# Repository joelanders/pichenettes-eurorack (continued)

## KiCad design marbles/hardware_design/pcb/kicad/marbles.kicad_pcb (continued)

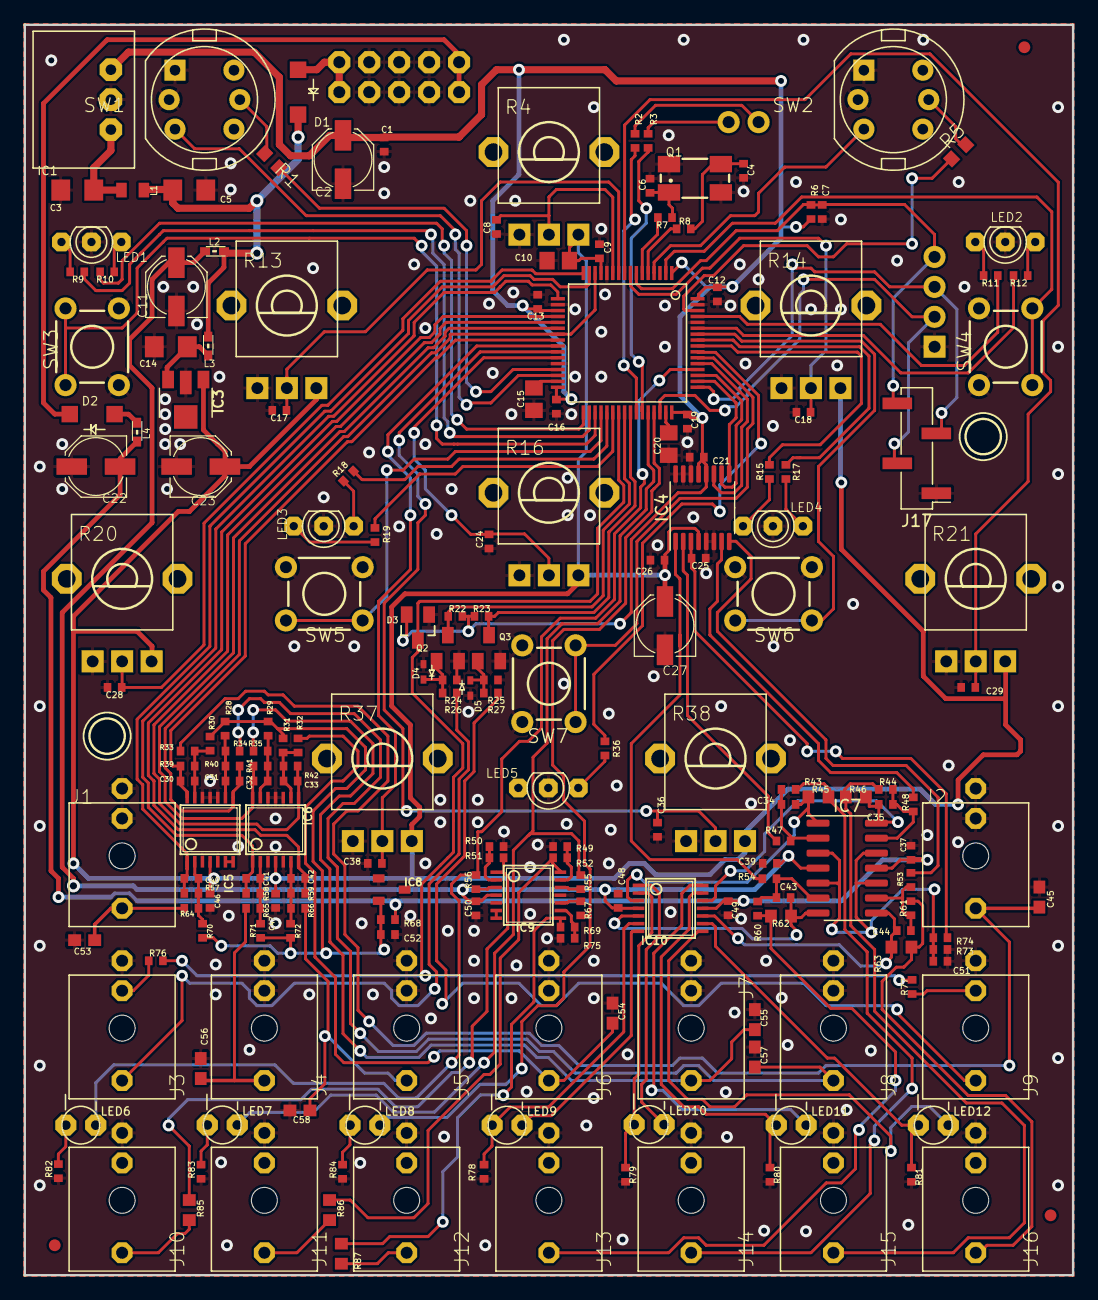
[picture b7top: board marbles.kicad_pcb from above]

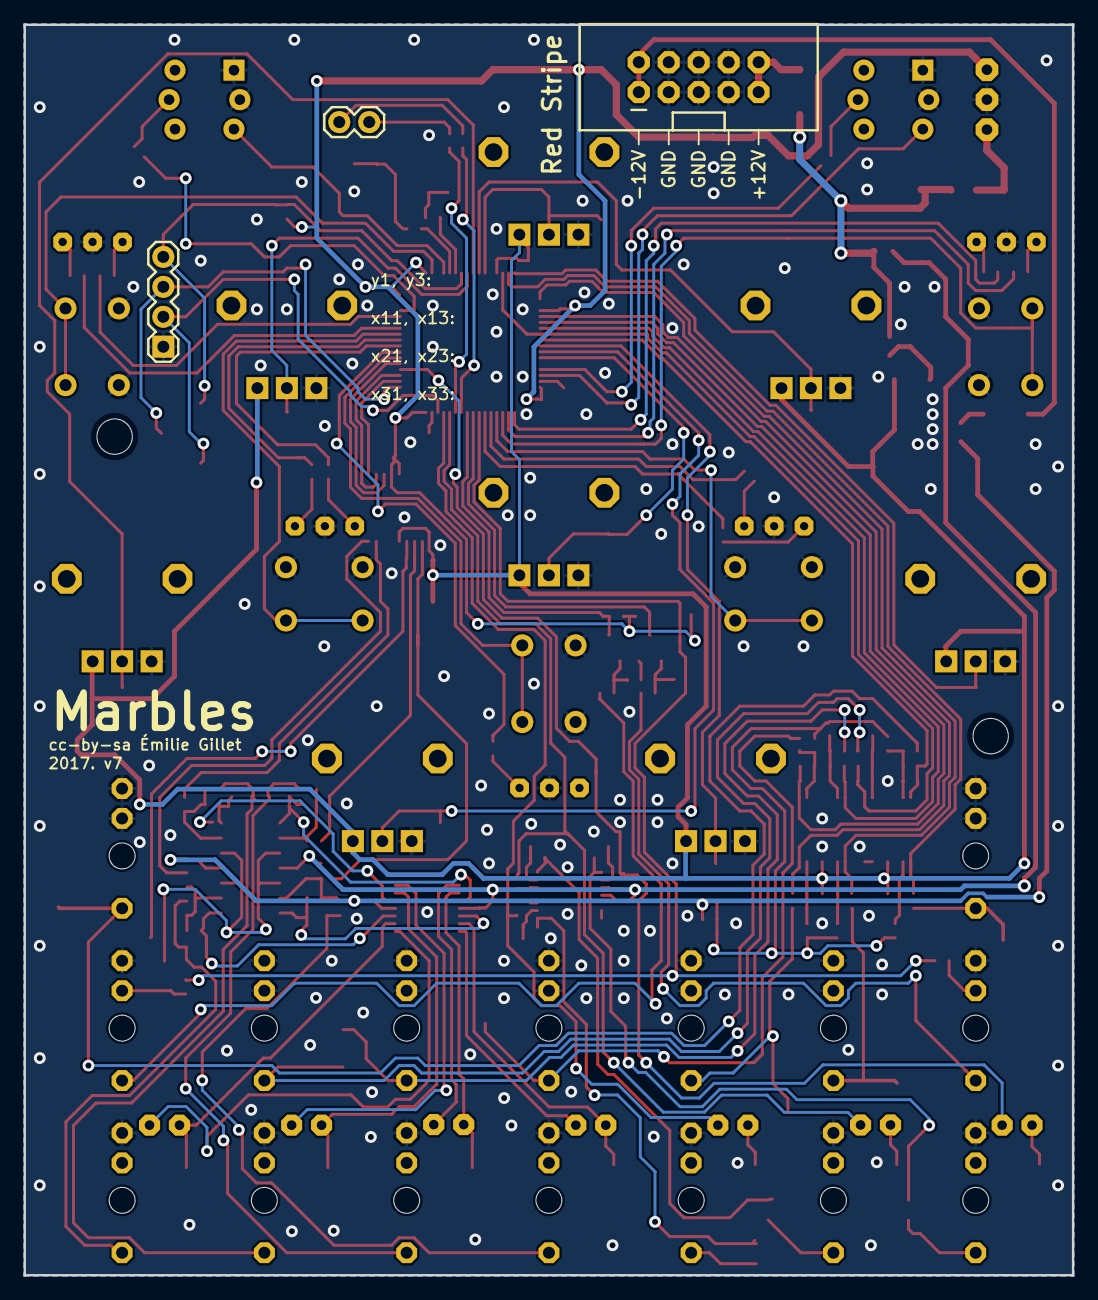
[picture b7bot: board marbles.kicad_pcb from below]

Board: 2 copper layers, 88.9 x 106.0 mm, 211 parts (3 on the bottom side), 141 nets.

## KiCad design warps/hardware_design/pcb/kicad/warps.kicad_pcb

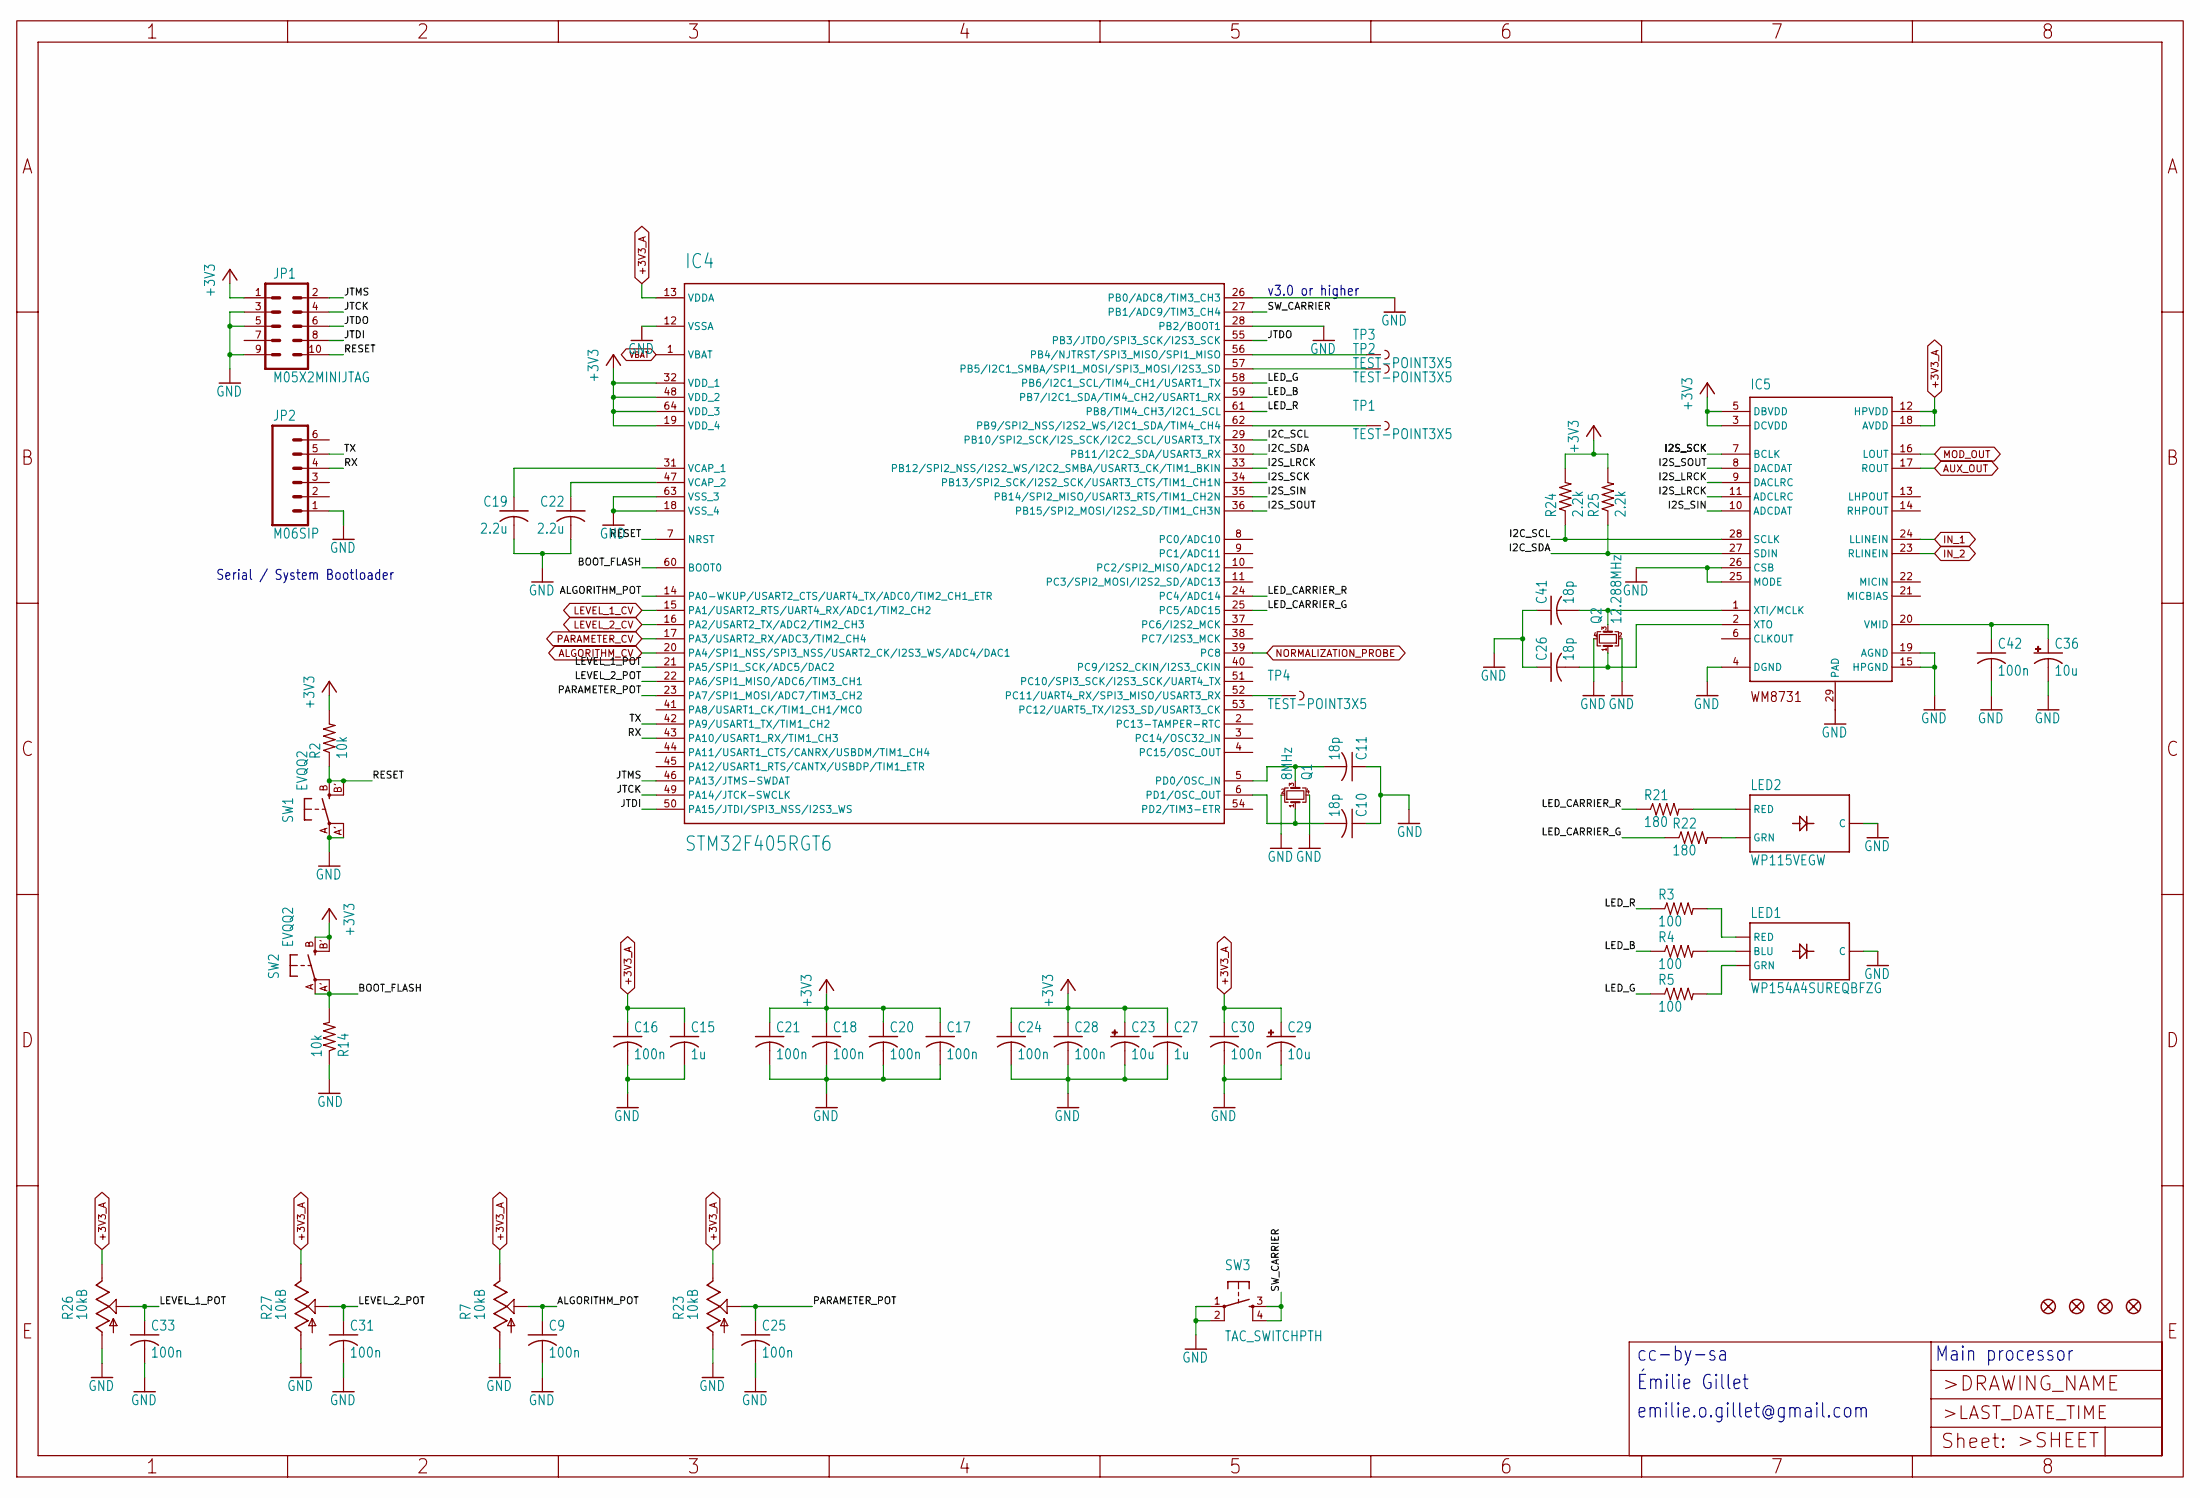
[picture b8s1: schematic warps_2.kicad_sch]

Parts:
C9, C16, C17, C18, C20, C21, C24, C25, C28, C30, C31, C33, C42: 100n; C0603
C10, C11, C26, C41: 18p; C0603
C15, C27: 1u; C0603
C19, C22: 2.2u; C0805
C23, C29, C36: 10u; PANASONIC_B
F1, F2, F3, F4: FIDUCIAL1X2; FIDUCIAL-1X2
IC4: STM32F405RGT6; TQFP-10X10-64
IC5: WM8731; QFN-28-1EP_5x5mm_P0.5mm_EP3.35x3.35mm
JP1: M05X2MINIJTAG; 2X5-1.27
JP2: M06SIP; 1X06
LED1: WP154A4SUREQBFZG; LED-TRICOLOR-THROUGHHOLE
LED2: WP115VEGW; LED-BICOLOR-THROUGHHOLE
Q1: 8MHz; Crystal_SMD_3225-4Pin_3.2x2.5mm
Q2: 12.288MHz; Crystal_SMD_5032-4Pin_5.0x3.2mm
R2, R14: 10k; R0603
R3, R4, R5: 100; R0603
R7, R23: 10kB; ALPS_POT_VERTICAL_PS
R21, R22: 180; R0603
R24, R25: 2.2k; R0603
R26, R27: 10kB; ALPS_POT_VERTICAL
SW1, SW2: EVQQ2; k2-1808 pushbutton switch
SW3: TAC_SWITCHPTH; TACTILE-PTH
TP1, TP2, TP3, TP4: TEST-POINT3X5; PAD.03X.05

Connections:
+3V3: C17.1, C18.1, C20.1, C21.1, C23.+, C24.1, C27.1, C28.1, IC4.19 (VDD_4), IC4.32 (VDD_1), IC4.48 (VDD_2), IC4.64 (VDD_3), IC5.3 (DCVDD), IC5.5 (DBVDD), JP1.1, R2.2, R24.2, R25.2, SW2.B (S), SW2.B' (S1); also elsewhere on the board
+3V3_A: C15.1, C16.1, C29.+, C30.1, IC4.13 (VDDA), IC5.12 (HPVDD), IC5.18 (AVDD), R7.P$1 (E), R23.P$1 (E), R26.P$1 (E), R27.P$1 (E); also elsewhere on the board
/warps_2/ALGORITHM_POT: C9.1, IC4.14 (PA0-WKUP/USART2_CTS/UART4_TX/ADC0/TIM2_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), R7.P$2 (S)
/warps_2/BOOT_FLASH: IC4.60 (BOOT0), R14.2, SW2.A, SW2.A' (P1)
/warps_2/I2C_SCL: IC4.29 (PB10/SPI2_SCK/I2S_SCK/I2C2_SCL/USART3_TX), IC5.28 (SCLK), R24.1
/warps_2/I2C_SDA: IC4.30 (PB11/I2C2_SDA/USART3_RX), IC5.27 (SDIN), R25.1
/warps_2/I2S_LRCK: IC4.33 (PB12/SPI2_NSS/I2S2_WS/I2C2_SMBA/USART3_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), IC5.9 (DACLRC), IC5.11 (ADCLRC)
/warps_2/I2S_SCK: IC4.34 (PB13/SPI2_SCK/I2S2_SCK/USART3_CTS/TIM1_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), IC5.7 (BCLK)
/warps_2/I2S_SIN: IC4.35 (PB14/SPI2_MISO/USART3_RTS/TIM1_CH2N), IC5.10 (ADCDAT)
/warps_2/I2S_SOUT: IC4.36 (PB15/SPI2_MOSI/I2S2_SD/TIM1_CH3N), IC5.8 (DACDAT)
/warps_2/JTCK: IC4.49 (PA14/JTCK-SWCLK), JP1.4
/warps_2/JTDI: IC4.50 (PA15/JTDI/SPI3_NSS/I2S3_WS), JP1.8
/warps_2/JTDO: IC4.55 (PB3/JTDO/SPI3_SCK/I2S3_SCK), JP1.6
/warps_2/JTMS: IC4.46 (PA13/JTMS-SWDAT), JP1.2
/warps_2/LED_B: IC4.59 (PB7/I2C1_SDA/TIM4_CH2/USART1_RX), R4.1
/warps_2/LED_CARRIER_G: IC4.25 (PC5/ADC15), R22.1
/warps_2/LED_CARRIER_R: IC4.24 (PC4/ADC14), R21.1
/warps_2/LED_G: IC4.58 (PB6/I2C1_SCL/TIM4_CH1/USART1_TX), R5.1
/warps_2/LED_R: IC4.61 (PB8/TIM4_CH3/I2C1_SCL), R3.1
/warps_2/LEVEL_1_POT: C33.1, IC4.21 (PA5/SPI1_SCK/ADC5/DAC2), R26.P$2 (S)
/warps_2/LEVEL_2_POT: C31.1, IC4.22 (PA6/SPI1_MISO/ADC6/TIM3_CH1), R27.P$2 (S)
/warps_2/PARAMETER_POT: C25.1, IC4.23 (PA7/SPI1_MOSI/ADC7/TIM3_CH2), R23.P$2 (S)
/warps_2/RESET: IC4.7 (NRST), JP1.10, R2.1, SW1.B (S), SW1.B' (S1)
/warps_2/RX: IC4.43 (PA10/USART1_RX/TIM1_CH3), JP2.4
/warps_2/SW_CARRIER: IC4.27 (PB1/ADC9/TIM3_CH4), SW3.3, SW3.4
/warps_2/TX: IC4.42 (PA9/USART1_TX/TIM1_CH2), JP2.5
ALGORITHM_CV: IC4.20 (PA4/SPI1_NSS/SPI3_NSS/USART2_CK/I2S3_WS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); also elsewhere on the board
AUX_OUT: IC5.17 (ROUT); also elsewhere on the board
GND: C9.2, C10.1, C11.1, C15.2, C16.2, C17.2, C18.2, C19.2, C20.2, C21.2, C22.2, C23.-, C24.2, C25.2, C26.1, C27.2, C28.2, C29.-, C30.2, C31.2, C33.2, C36.-, C41.1, C42.2, IC4.12 (VSSA), IC4.18 (VSS_4), IC4.26 (PB0/ADC8/TIM3_CH3), IC4.28 (PB2/BOOT1), IC4.63 (VSS_3), IC5.4 (DGND), IC5.15 (HPGND), IC5.19 (AGND), IC5.25 (MODE), IC5.26 (CSB), IC5.29 (PAD), JP1.3, JP1.5, JP1.9, JP2.1, LED1.GND (C), LED2.2 (C), Q1.2, Q1.4, Q2.2, Q2.4, R7.P$3 (A), R14.1, R23.P$3 (A), R26.P$3 (A), R27.P$3 (A), SW1.A, SW1.A' (P1), SW3.1, SW3.2; also elsewhere on the board
IN_1: IC5.24 (LLINEIN); also elsewhere on the board
IN_2: IC5.23 (RLINEIN); also elsewhere on the board
LEVEL_1_CV: IC4.15 (PA1/USART2_RTS/UART4_RX/ADC1/TIM2_CH2); also elsewhere on the board
LEVEL_2_CV: IC4.16 (PA2/USART2_TX/ADC2/TIM2_CH3); also elsewhere on the board
MOD_OUT: IC5.16 (LOUT); also elsewhere on the board
NORMALIZATION_PROBE: IC4.39 (PC8); also elsewhere on the board
unnamed: C10.2, IC4.6 (PD1/OSC_OUT), Q1.1
unnamed: C11.2, IC4.5 (PD0/OSC_IN), Q1.3
unnamed: C19.1, IC4.31 (VCAP_1)
unnamed: C22.1, IC4.47 (VCAP_2)
unnamed: C26.2, IC5.2 (XTO), Q2.1
unnamed: C36.+, C42.1, IC5.20 (VMID)
unnamed: C41.2, IC5.1 (XTI/MCLK), Q2.3
unnamed: IC4.52 (PC11/UART4_RX/SPI3_MISO/USART3_RX), TP4.P$1 (1)
unnamed: IC4.56 (PB4/NJTRST/SPI3_MISO/SPI1_MISO), TP3.P$1 (1)
unnamed: IC4.57 (PB5/I2C1_SMBA/SPI1_MOSI/SPI3_MOSI/I2S3_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), TP2.P$1 (1)
unnamed: IC4.62 (PB9/SPI2_NSS/I2S2_WS/I2C1_SDA/TIM4_CH4), TP1.P$1 (1)
unnamed: LED1.BLU, R4.2
unnamed: LED1.GRN, R5.2
unnamed: LED1.RED, R3.2
unnamed: LED2.1 (GRN), R22.2
unnamed: LED2.3 (RED), R21.2
PARAMETER_CV: IC4.17 (PA3/USART2_RX/ADC3/TIM2_CH4); also elsewhere on the board
VBAT: IC4.1 (VBAT)

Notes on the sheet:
Émilie Gillet
emilie.o.gillet@gmail.com
Serial / System Bootloader
Main processor
cc-by-sa
v3.0 or higher

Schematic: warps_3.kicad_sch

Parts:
C7, C8, C12, C14: 4.7n; C0603
C13, C34, C40: 100n; C0603
C32, C37, C39, C43: 10u; PANASONIC_B
C35, C38: 18p; C0603
C44, C45: 220p; C0603
D3: BAT54S; SOT23
IC3: MCP6004; SO14
IC6: TL072; SO08
J1, J2, J3, J4, J5, J6, J7, J8: PJ301_THONKICONN6; WQP_PJ_301M6
R8, R9, R17, R18: 100k; R0603
R10, R11: 120k; R0603
R12, R13, R37, R38: 36k; R0603
R15, R16: 33k; R0603
R19, R20, R32, R35: 200k; R0603
R28, R30, R31, R33: 47k; R0603
R29, R34, R36, R39: 6.8k; R0603
R40, R41: DNP; R0603
R42, R43: 1.0k; R0603

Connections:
+3V3: D3.2 (C); also elsewhere on the board
+3V3_A: C13.1, IC3.4 (V+); also elsewhere on the board
ALGORITHM_CV: C12.2, IC3.1 (OUT), R15.1; also elsewhere on the board
AREF_-10: R10.2, R11.2, R19.2, R20.2; also elsewhere on the board
AUX_OUT: C39.+; also elsewhere on the board
GND: C13.2, C34.2, C40.1, C44.2, C45.2, D3.1 (A), IC3.3 (+IN), IC3.5 (+IN), IC3.10 (+IN), IC3.11 (V-), IC3.12 (+IN), IC6.3 (+IN), IC6.5 (+IN), J1.P1 (1), J2.P1 (1), J3.P1 (1), J4.P1 (1), J5.P1 (1), J6.P1 (1), J7.P1 (1), J8.P1 (1), R28.1, R33.1, R36.1, R39.1; also elsewhere on the board
IN_1: C37.+; also elsewhere on the board
IN_2: C43.+; also elsewhere on the board
LEVEL_1_CV: C8.2, IC3.8 (OUT), R13.1; also elsewhere on the board
LEVEL_2_CV: C7.2, IC3.14 (OUT), R12.1; also elsewhere on the board
MOD_OUT: C32.+; also elsewhere on the board
NORMALIZATION_PROBE: D3.3 (AC), R32.1, R35.1, R40.2, R41.2; also elsewhere on the board
unnamed: C7.1, IC3.13 (-IN), R8.1, R10.1, R12.2
unnamed: C8.1, IC3.9 (-IN), R9.1, R11.1, R13.2
unnamed: C12.1, IC3.2 (-IN), R15.2, R17.1, R19.1
unnamed: C14.1, IC3.6 (-IN), R16.2, R18.1, R20.1
unnamed: C32.-, R28.2, R29.2
unnamed: C35.1, IC6.2 (-IN), R29.1, R30.2
unnamed: C35.2, IC6.1 (OUT), R30.1, R42.2
unnamed: C37.-, C44.1, R36.2, R37.1
unnamed: C38.1, IC6.6 (-IN), R31.2, R34.1
unnamed: C38.2, IC6.7 (OUT), R31.1, R43.2
unnamed: C39.-, R33.2, R34.2
unnamed: C43.-, C45.1, R38.1, R39.2
unnamed: J1.P2 (2), R32.2
unnamed: J1.P3 (3), R9.2
unnamed: J2.P2 (2), R35.2
unnamed: J2.P3 (3), R8.2
unnamed: J3.P3 (3), R17.2
unnamed: J4.P3 (3), R18.2
unnamed: J5.P2 (2), R40.1
unnamed: J5.P3 (3), R37.2
unnamed: J6.P2 (2), R41.1
unnamed: J6.P3 (3), R38.2
unnamed: J7.P3 (3), R42.1
unnamed: J8.P3 (3), R43.1
PARAMETER_CV: C14.2, IC3.7 (OUT), R16.1; also elsewhere on the board
VCC: C34.1, IC6.8 (V+); also elsewhere on the board
VEE: C40.2, IC6.4 (V-); also elsewhere on the board

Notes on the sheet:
-1V to 8V
-5V to 5V
Analog
cc-by-sa
Émilie Gillet
emilie.o.gillet@gmail.com

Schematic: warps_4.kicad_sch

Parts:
C1, C2, C3, C4: 47u; PANASONIC_D
C5, C6: 100n; C0603
D1, D2: 1N5819HW; SOD123
IC1: LM1117-3.3; TO252
IC2: LM4040B10; DBZ_R-PDSO-G3
JP3: M05X2PTH; AVR_ICSP
L1, L2, L3: WE-CBF_0603; 0603
R1: 4.7; R1206
R6: 4.7k; R0603

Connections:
+3V3: C4.+, C5.1, IC1.3 (VOUT), L2.1; also elsewhere on the board
+3V3_A: L2.2; also elsewhere on the board
AREF_-10: C6.1, IC2.2 (A), R6.2; also elsewhere on the board
GND: C1.-, C2.-, C3.+, C4.-, C5.2, C6.2, IC1.1 (GND), IC2.1 (C), JP3.3, JP3.4, JP3.5, JP3.6, JP3.7, JP3.8; also elsewhere on the board
unnamed: C2.+, IC1.2 (VIN), R1.1
unnamed: D1.A, JP3.1, JP3.2
unnamed: D1.C, L1.2
unnamed: D2.A, L3.2
unnamed: D2.C, JP3.9, JP3.10
VCC: C1.+, L1.1, R1.2; also elsewhere on the board
VEE: C3.-, L3.1, R6.1; also elsewhere on the board

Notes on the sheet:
266µA
emilie.o.gillet@gmail.com
cc-by-sa
Émilie Gillet
Supply

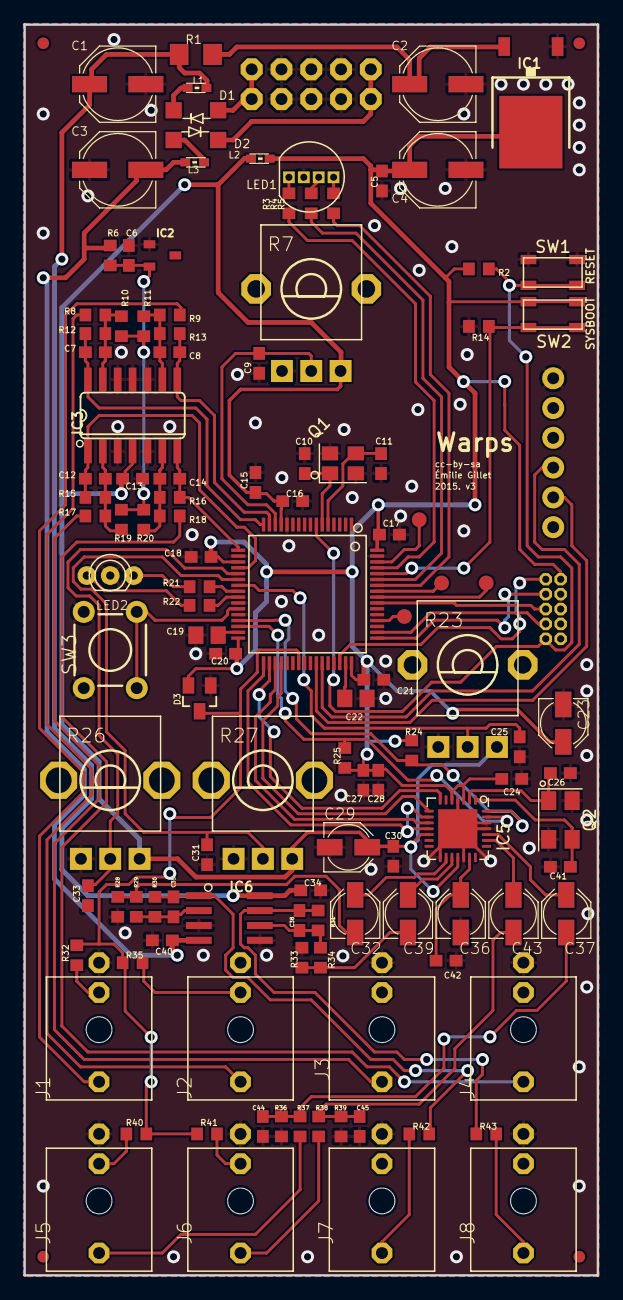
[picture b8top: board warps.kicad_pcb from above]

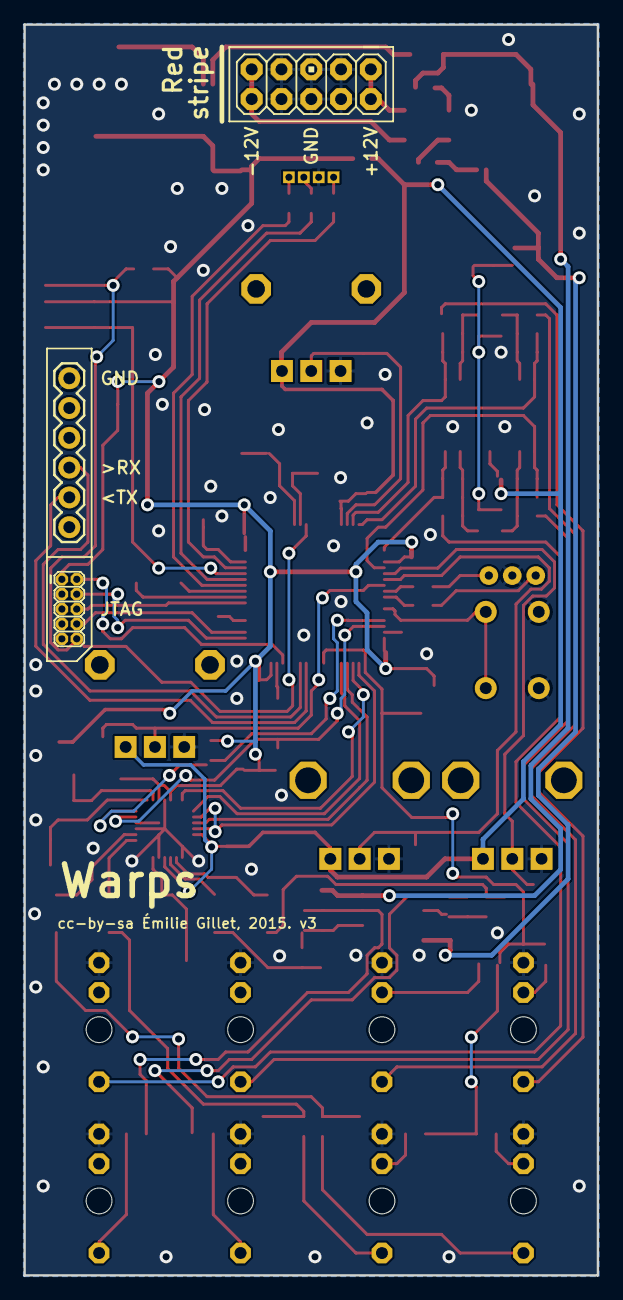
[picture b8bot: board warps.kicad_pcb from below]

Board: 2 copper layers, 48.9 x 106.7 mm, 126 parts (3 on the bottom side), 84 nets.

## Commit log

2023-03-04 grids eagle 7
2023-03-04 grids kicad initial import
2023-03-04 change LED/SW and crystal
2023-03-04 fp-info-cache, dunno what this is
2023-03-04 add horizontal smd programming header (traces not drawn yet)
2023-03-04 changed jacks
2023-03-04 draw pcb traces for new header
2023-03-04 add 0603 LEDs in parallel with other footprint
2023-03-04 change the jack again
2023-03-04 some random ctrl-s
2023-03-04 braids eagle7
2023-03-04 braids kicad import
2023-03-04 add surfact mount serial flashing header
2023-03-04 move new header
2023-03-04 re-routing some traces around the jtag connector
2023-03-04 fix DRC
2023-03-04 elements eagle 7
2023-03-04 elements kicad import
2023-03-04 braids fp-info-cache
2023-03-04 changed led/switch
2023-03-04 change LME49720 to tl072
2023-03-04 swap wm8731 package (haven't drawn traces yet)
2023-03-05 traces drawn for wm8731
2023-03-05 smaller boot/reset buttons
2023-03-05 SMD LEDs
2023-03-05 add optional SMD power
2023-03-05 ground fill?
2023-03-05 marbles eagle7
2023-03-05 marbles kicad import
2023-03-05 replace led/button switches
2023-03-05 added SMD LEDs in parallel with THT footprint
2023-03-05 bottom row output LEDs to SMD
2023-03-05 unfill
2023-03-05 marbles fp-info-cache
2023-03-05 elements active layer
2023-03-06 marbles jlc plugin first run
2023-03-06 .gitignore -- don't ignore csv files
2023-03-06 changed opa4174 package
2023-03-06 change dac from 8164 to 8565
2023-03-06 add smd flash header in parallel
2023-03-06 ran the jlc plugin
2023-03-06 run my script
2023-03-06 fill in some JLC part numbers
2023-03-06 re-add ferrite bead part number (0603 gets turned to 603)
2023-03-06 grids: ran JLC plugin
2023-03-06 fill in some grids components
2023-03-06 braids: ran plugin
2023-03-06 ran my script
2023-03-06 changed mcp3204 to mcp3208
2023-03-06 ran plugin
2023-03-06 ran script
2023-03-06 elements: ran plugin
2023-03-06 elements: run script
2023-03-06 add stuff to elements BOM
2023-03-06 finish grids bom
2023-03-07 add some more components to EXCEL FILES
2023-03-07 marbles: add orientation silkscreen to diodes
2023-03-07 better LED silkscreen positions
2023-03-07 elements: add silkscreen to diodes
2023-03-07 elements silkscreen
2023-03-07 silkscreen
2023-03-07 run plugin
2023-03-07 fix rotations
2023-03-07 elements CPL excel spreadsheet (XXX)
2023-03-08 CPL marbles excel spreadsheet (XXX)
2023-03-08 marbles CPL: somewhere these decimal points got dropped (XXX)
2023-03-11 all the latest shit needed for jlc
2023-03-28 change footprint to match 0805 LED
2023-03-28 change LED part number in BOM excel
2023-03-28 change two 39 ohm 0402 resistors to 1k 0603
2023-03-28 change same resistors in BOM excel
2023-03-28 add orientation silk to d4 and d5
2023-04-24 slightly enlarge SMD LED pads, generate gerbers (USE MY OLD NEW BOM THOUGH)
2023-04-24 use the previous CPL excel file
2023-04-24 new CPL excel sheet for marbles
2023-04-24 braids bom excel from csv
2023-04-24 plaits eagle7
2023-04-24 plaits kicad
2023-04-24 plaits run a quick production file export
2023-04-25 plaits bom
2023-04-25 plaits silkscreen + CPL excel
2023-04-25 update pcb from schematic (no change but it removed some logos)
2023-04-29 rings initial import, conversion, prod file generation
2023-05-02 rings fill?
2023-05-02 kinks import
2023-05-02 links import
2023-05-20 specify serial port in rings makefile
2023-05-21 clouds initial import from eagle
2023-05-21 clouds pristine production file generation
2023-05-21 clouds wm8731 schematic update
2023-05-21 clouds wm8731 QFN on PCB. also panasonic a -> b caps
2023-05-21 cap spacing
2023-05-21 clouds SMD reset + boot buttons
2023-05-21 clouds new kind of LED/switch pushbutton
2023-05-21 clouds: thonk/alpha dual gang pot
2023-05-21 screenprint orientation diodes + op amps
2023-05-25 clouds fp-info-cache
2023-05-25 kinks fp-info-cache
2023-05-25 warps initial kicad import
2023-05-25 warps caps + wm8731
2023-05-25 warps cleanup tracks and vias
2023-05-25 warps SMD boot/reset buttons
2023-05-25 warps diode + op amp orientation silkscreen
2023-05-25 marbles remove SMD LEDs, revert to THT
2023-05-25 marbles bigger LED + switch pads
2023-05-25 clouds larger switch pads
2023-05-25 warps larger LED pads
2023-05-25 plaits larger LED pads
2023-05-25 plaits clean up traces + vias
2023-05-25 plaits resized panasonic A -> B caps
2023-05-26 tides2 initial import
2023-05-26 replace tssop tlv op amp with soic
2023-05-26 tides2 cleanup
2023-05-26 tides2 dac8164 -> dac8565
2023-05-26 clouds BOM (most of it) and production files
2023-05-26 clouds bom
2023-05-26 warps production files and BOM
2023-05-26 tides2 initial prod files + BOM
2023-05-26 plaits NOTE XXX: power inductor should be larger
2023-05-26 tides2 BOM
2023-05-26 clouds, tides, warps excel BOMs
2023-05-28 clouds cleanup
2023-05-28 tides2 fp-info-cache
2023-05-28 warps panel svg
2023-05-28 warps autosave bullshit?
2023-05-28 warps unfill
2023-05-28 warps extra via
2023-05-29 clouds net names changed?
2023-05-29 clouds final tweaks
2023-05-29 warps final tweaks
2023-05-29 warps fill
2023-05-29 tides final tweaks
2023-05-31 clouds, tides2, warps numbers bom spreadsheets
2023-07-16 marbles change button LEDs from 1k to 680R
2023-07-16 marbles silkscreen for calibration readings
2023-07-16 marbles rotate output LEDs to match original
2023-07-16 marbles generate prod files with plugin
2023-07-16 marbles bom: use correct lm4040 and new led resistors
2023-08-25 plaits tweaks
2023-08-25 peaks initial kicad import
2023-08-26 branches: initial kicad import
2023-08-26 peaks: smd boot + reset buttons
2023-08-26 peaks: diode silkscreen
2023-08-26 peaks: led/button footprint change
2023-08-26 peaks: change led resistor from 33 to 680 ohms
2023-08-26 peaks: led button silkscren polarity
2023-08-28 peaks: panel in kicad
2023-09-08 links: move LEDs to left side
2023-09-09 links: change panasonic A to 3x5.3mm footprint
2023-09-10 kinks
2023-09-10 links
2023-09-10 peaks
2023-10-27 tides2 unsaved changes
2023-10-27 peaks unsaved changes
2023-10-27 links unsaved changes
2023-10-27 kinks unsaved changes
2024-02-10 rings changes
2024-02-10 clouds changes
2024-02-10 marbles kicad state
2024-07-07 small unimportant metadata things
2024-07-07 add plaits gerber zip
